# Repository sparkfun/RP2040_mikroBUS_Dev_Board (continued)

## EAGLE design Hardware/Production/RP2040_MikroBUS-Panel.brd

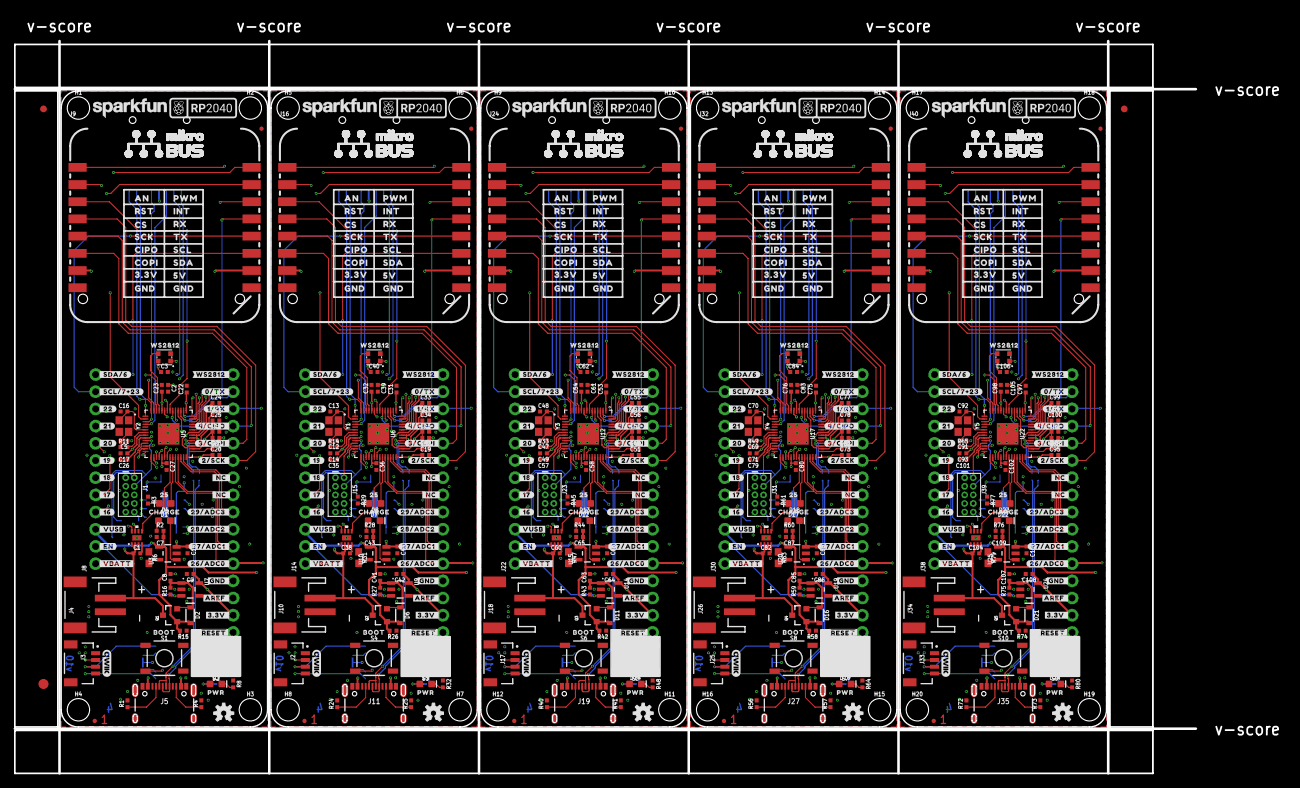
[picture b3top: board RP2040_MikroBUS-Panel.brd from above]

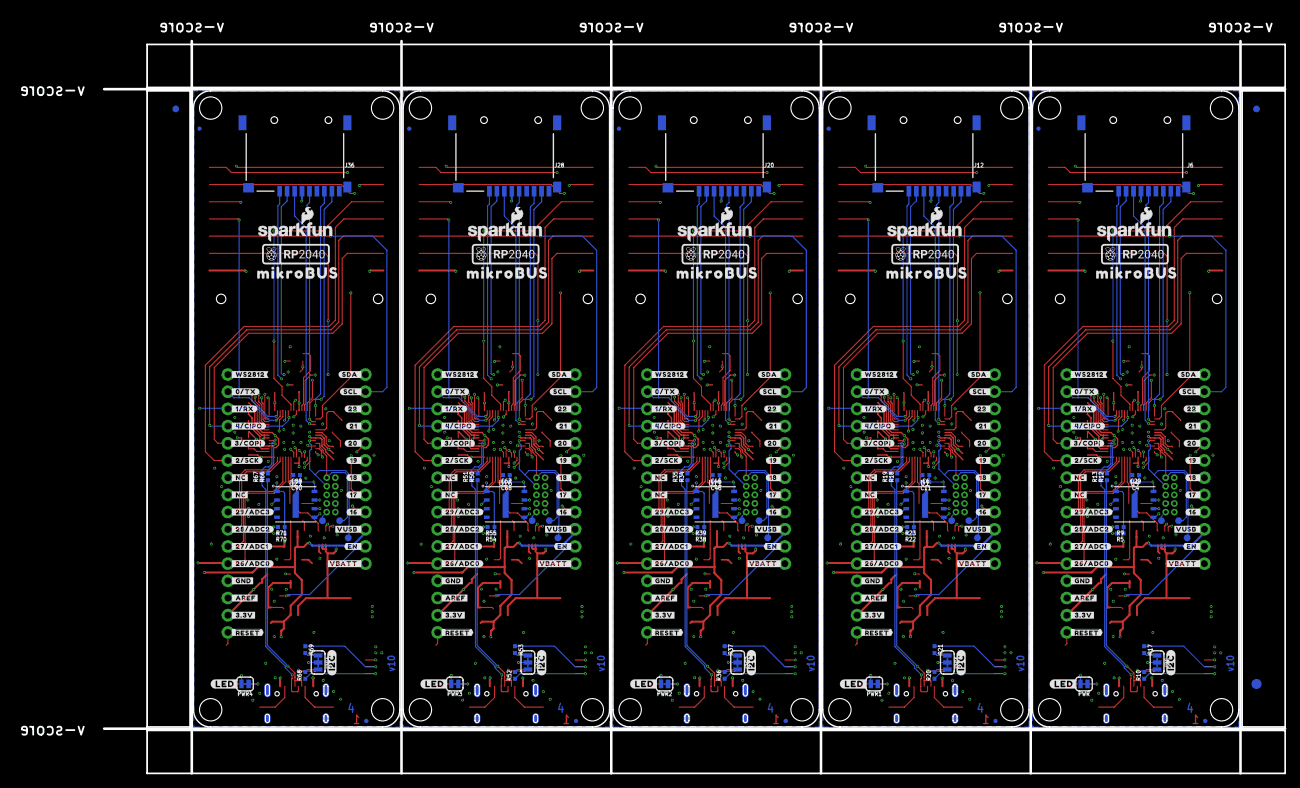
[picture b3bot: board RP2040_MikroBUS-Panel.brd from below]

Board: 4 copper layers, 174.5 x 108.2 mm, 801 parts (253 on the bottom side), 325 nets.

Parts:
C1, C2, C3, C6, C14, C15, C17, C18, C19, C20, C21, C22, C23, C24, C25, C29, C30, C31, C32, C33, C34, C38, C39, C40, C45, C49, C50, C51, C52, C53, C54, C55, C56, C60, C61, C62, C67, C71, C72, C73, C74, C75, C76, C77, C78, C82, C83, C84, C89, C93, C94, C95, C96, C97, C98, C99, C100, C104, C105, C106: 0.1uF; 0402-TIGHT
C4, C9, C11, C26, C27, C28, C35, C36, C37, C42, C46, C57, C58, C59, C64, C68, C79, C80, C81, C86, C90, C101, C102, C103, C108: 2.2uF; 0402-TIGHT
C5, C12, C13, C16, C47, C48, C69, C70, C91, C92: 15pF; 0402-TIGHT
C7, C10, C43, C44, C65, C66, C87, C88, C109, C110: 4.7uF; 0402-TIGHT
C8, C41, C63, C85, C107: 1.0uF; 0402-TIGHT
D1, D7, D12, D17, D22: Yellow; LED-0603
D2, D6, D11, D16, D21: 1A/23V/620mV; SOD-323
D3, D9, D14, D19, D24: RED; LED-0603
D4, D8, D13, D18, D23: BLUE; LED-0603
D5, D10, D15, D20, D25: WS2812_2020; WS2812-2020
E$1, E$2, E$3, E$4: FIDUCIAL-1X2
E$5, E$6: FIDUCIAL-1.5X3
FD1, FD2, FD3, FD4, FD5, FD6, FD7, FD8, FD9, FD10, FD11, FD12, FD13, FD14, FD15, FD16, FD17, FD18, FD19, FD20: FIDUCIALUFIDUCIAL; FIDUCIAL-MICRO
H1, H2, H3, H4, H5, H6, H7, H8, H9, H10, H11, H12, H13, H14, H15, H16, H17, H18, H19, H20: STAND-OFF
I2C, I2C1, I2C2, I2C3, I2C4: JUMPER-SMT_3_2-NC_TRACE_SILK; SMT-JUMPER_3_2-NC_TRACE_SILK
J1, J15, J23, J31, J39: SWD; 2X5-PTH-1.27MM
J2, J3, J17, J25, J33: Qwiic; JST04_1MM_RA
J4, J10, J18, J26, J34: JST-2-SMD
J5, J11, J19, J27, J35: USB C; USB-C-16P-4LAYER-ISOLATED
J6, J12, J20, J28, J36: microSD; MICROSD-EXTERNALPIN
J7, J13, J21, J29, J37: 1X16_NO_SILK
J8, J14, J22, J30, J38: 1X12_NO_SILK
J9, J16, J24, J32, J40: MIKROBUS_SMD_BLACK1; MIKROBUS_SMD_BLACK
LOGO1, LOGO3, LOGO5, LOGO7, LOGO9: OSHW-LOGOS; OSHW-LOGO-S
LOGO2, LOGO4, LOGO6, LOGO8, LOGO10: SFE_LOGO_NAME.1_INCH; SFE_LOGO_NAME_.1
PWR, PWR1, PWR2, PWR3, PWR4: JUMPER-SMT_2_NC_TRACE_SILK; SMT-JUMPER_2_NC_TRACE_SILK
Q1, Q2, Q3, Q4, Q5: 20V/4.2A/52mΩ/1.4W; SOT23-3
R1, R4, R24, R25, R40, R41, R56, R57, R72, R73: 5.1k; 0402-TIGHT
R2, R3, R5, R8, R11, R14, R22, R28, R29, R32, R33, R38, R44, R45, R48, R49, R54, R60, R61, R64, R65, R70, R76, R77, R80: 1k; 0402-TIGHT
R6, R31, R47, R63, R79: 2.0k; 0603
R7, R30, R46, R62, R78: 200OHM-0402T-1/16W-1%; 0402-TIGHT
R9, R15, R16, R23, R26, R27, R39, R42, R43, R55, R58, R59, R71, R74, R75: 10k; 0402-TIGHT
R10, R17, R20, R21, R36, R37, R52, R53, R68, R69: 2.2k; 0402-TIGHT
R12, R13, R18, R19, R34, R35, R50, R51, R66, R67: 27; 0402-TIGHT
S1, S2, S3, S4, S5, S6, S7, S8, S9, S10: MOMENTARY-SWITCH-SPST-SMD-5.2MM-TALL; TACTILE_SWITCH_SMD_5.2MM
TP1, TP2, TP3, TP4, TP5, TP6, TP7, TP8, TP9, TP10, TP11, TP12, TP13, TP14, TP15: TEST-POINT3X4; PAD.03X.04
U1, U4, U11, U16, U21: W25QXX128MBIT; WSON-8-6X5-SKINNY_CENTERPAD
U2, U8, U13, U18, U23: MAX17048; DFN-8
U3, U10, U15, U20, U25: MCP73831; SOT23-5
U5, U6, U12, U17, U22: RP2040; QFN-56
U7, U9, U14, U19, U24: 3.3V; SOT23-5
U$1, U$31, U$169, U$253, U$337: #_16#0
U$2, U$46, U$170, U$254, U$338: #_17#0
U$3, U$86, U$171, U$255, U$339: #_18#0
U$4, U$87, U$172, U$256, U$340: #_19#0
U$5, U$89, U$173, U$257, U$341: #_20#0
U$6, U$90, U$174, U$258, U$342: #_21#0
U$7, U$91, U$175, U$259, U$343: #_22#0
U$8, U$98, U$182, U$266, U$350: #_SCL#7#23#0
U$9, U$99, U$183, U$267, U$351: #_SDA#6#0
U$10, U$92, U$176, U$260, U$344: #WS2812_#0
U$11, U$93, U$177, U$261, U$345: #0#TX_#0
U$12, U$94, U$178, U$262, U$346: #1#RX_#0
U$13, U$95, U$179, U$263, U$347: #4#CIPO_#0
U$14, U$96, U$180, U$264, U$348: #3#COPI_#0
U$15, U$97, U$181, U$265, U$349: #2#SCK_#0
U$16, U$138, U$222, U$306, U$390: PWR0
U$17, U$73, U$148, U$149, U$232, U$233, U$316, U$317, U$400, U$401: RASPI_RP2040_LOGO_10MM
U$18, U$100, U$184, U$268, U$352: #29#ADC3_#0
U$19, U$101, U$185, U$269, U$353: #28#ADC2_#0
U$20, U$102, U$186, U$270, U$354: #27#ADC1_#0
U$21, U$103, U$187, U$271, U$355: #26#ADC0_#0
U$22, U$104, U$188, U$272, U$356: #_VUSB#0
U$23, U$105, U$189, U$273, U$357: #_EN#0
U$24, U$106, U$190, U$274, U$358: #_VBATT#0
U$25, U$107, U$191, U$275, U$359: #GND_#0
U$26, U$108, U$192, U$276, U$360: #AREF_#0
U$27, U$109, U$193, U$277, U$361: #3#3V_#0
U$28, U$110, U$194, U$278, U$362: ##RESET##0
U$29, U$151, U$235, U$319, U$403: AN0
U$30, U$150, U$234, U$318, U$402: WS28120
U$32, U$112, U$196, U$280, U$364: SFE_LOGO_NAME_FLAME_.1
U$33, U$126, U$210, U$294, U$378: #SCL_#0
U$34, U$127, U$211, U$295, U$379: #SDA_#0
U$35, U$128, U$212, U$296, U$380: #_#RESET##0
U$36, U$129, U$213, U$297, U$381: #_3#3V#0
U$37, U$130, U$214, U$298, U$382: #_AREF#0
U$38, U$131, U$215, U$299, U$383: #_GND#0
U$39, U$132, U$216, U$300, U$384: #_26#ADC0#0
U$40, U$133, U$217, U$301, U$385: #_27#ADC1#0
U$41, U$134, U$218, U$302, U$386: #_28#ADC2#0
U$42, U$135, U$219, U$303, U$387: #_29#ADC3#0
U$43, U$168, U$252, U$336, U$420: #LED#0
U$44, U$152, U$236, U$320, U$404: RST0
U$45, U$153, U$237, U$321, U$405: CS0
U$47, U$48, U$139, U$140, U$223, U$224, U$307, U$308, U$391, U$392: #_NC_#0
U$49, U$141, U$225, U$309, U$393: #_2#SCK#0
U$50, U$142, U$226, U$310, U$394: #_3#COPI#0
U$51, U$143, U$227, U$311, U$395: #_4#CIPO#0
U$52, U$144, U$228, U$312, U$396: #_1#RX#0
U$53, U$145, U$229, U$313, U$397: #_0#TX#0
U$54, U$113, U$197, U$281, U$365: 250
U$55, U$114, U$198, U$282, U$366: CHARGE0
U$56, U$115, U$199, U$283, U$367: BOOT0
U$57, U$116, U$200, U$284, U$368: #22_#0
U$58, U$117, U$201, U$285, U$369: #21_#0
U$59, U$118, U$202, U$286, U$370: #20_#0
U$60, U$154, U$238, U$322, U$406: CIPO0
U$61, U$119, U$203, U$287, U$371: #19_#0
U$62, U$120, U$204, U$288, U$372: #18_#0
U$63, U$121, U$205, U$289, U$373: #17_#0
U$64, U$111, U$195, U$279, U$363: QWIIC_4MM
U$65, U$122, U$206, U$290, U$374: #16_#0
U$66, U$123, U$207, U$291, U$375: #VUSB_#0
U$67, U$124, U$208, U$292, U$376: #EN_#0
U$68, U$125, U$209, U$293, U$377: #VBATT_#0
U$69, U$70, U$136, U$137, U$220, U$221, U$304, U$305, U$388, U$389: #_NC#0
U$71, U$146, U$230, U$314, U$398: #_WS2812#0
U$72, U$147, U$231, U$315, U$399: #I2C#0
U$74, U$155, U$239, U$323, U$407: SCK0
U$75, U$156, U$240, U$324, U$408: COPI0
U$76, U$157, U$241, U$325, U$409: 3#3V0
U$77, U$78, U$158, U$159, U$242, U$243, U$326, U$327, U$410, U$411: GND0
U$79, U$160, U$244, U$328, U$412: 5V0
U$80, U$161, U$245, U$329, U$413: SDA0
U$81, U$162, U$246, U$330, U$414: SCL0
U$82, U$163, U$247, U$331, U$415: TX0
U$83, U$164, U$248, U$332, U$416: RX0
U$84, U$165, U$249, U$333, U$417: INT0
U$85, U$166, U$250, U$334, U$418: PWM0
U$88, U$167, U$251, U$335, U$419: MIKROBUS0
Y1, Y2, Y3, Y4, Y5: 12MHz; CRYSTAL-SMD-2X2.5MM

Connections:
1.1V: C24.1, C25.1, C26.1, U5.23, U5.45, U5.50
1.1V1: C33.1, C34.1, C35.1, U6.23, U6.45, U6.50
1.1V2: C55.1, C56.1, C57.1, U12.23, U12.45, U12.50
1.1V3: C77.1, C78.1, C79.1, U17.23, U17.45, U17.50
1.1V4: C99.1, C100.1, C101.1, U22.23, U22.45, U22.50
3.3V: C2.1, C3.1, C4.1, C9.1, C17.1, C18.1, C20.1, C21.1, C22.1, C23.1, C27.1, C29.1, D5.VCC, I2C.2, J1.1, J3.2, J6.4, J7.2, J9.7, PWR.2, R7.2, R9.2, U4.8, U5.1, U5.10, U5.22, U5.33, U5.42, U5.44, U5.48, U5.49, U7.5
3.3V1: C6.1, C11.1, C14.1, C15.1, C19.1, C30.1, C31.1, C32.1, C36.1, C39.1, C40.1, C42.1, D10.VCC, I2C1.2, J2.2, J12.4, J13.2, J15.1, J16.7, PWR1.2, R23.2, R30.2, U1.8, U6.1, U6.10, U6.22, U6.33, U6.42, U6.44, U6.48, U6.49, U9.5
3.3V2: C45.1, C46.1, C49.1, C50.1, C51.1, C52.1, C53.1, C54.1, C58.1, C61.1, C62.1, C64.1, D15.VCC, I2C2.2, J17.2, J20.4, J21.2, J23.1, J24.7, PWR2.2, R39.2, R46.2, U11.8, U12.1, U12.10, U12.22, U12.33, U12.42, U12.44, U12.48, U12.49, U14.5
3.3V3: C67.1, C68.1, C71.1, C72.1, C73.1, C74.1, C75.1, C76.1, C80.1, C83.1, C84.1, C86.1, D20.VCC, I2C3.2, J25.2, J28.4, J29.2, J31.1, J32.7, PWR3.2, R55.2, R62.2, U16.8, U17.1, U17.10, U17.22, U17.33, U17.42, U17.44, U17.48, U17.49, U19.5
3.3V4: C89.1, C90.1, C93.1, C94.1, C95.1, C96.1, C97.1, C98.1, C102.1, C105.1, C106.1, C108.1, D25.VCC, I2C4.2, J33.2, J36.4, J37.2, J39.1, J40.7, PWR4.2, R71.2, R78.2, U21.8, U22.1, U22.10, U22.22, U22.33, U22.42, U22.44, U22.48, U22.49, U24.5
!BATT_ALERT!: U2.5, U5.36
!BATT_ALERT!1: U6.36, U8.5
!BATT_ALERT!2: U12.36, U13.5
!BATT_ALERT!3: U17.36, U18.5
!BATT_ALERT!4: U22.36, U23.5
!BOOT!: R5.2, S1.3
!BOOT!1: R22.2, S4.3
!BOOT!2: R38.2, S6.3
!BOOT!3: R54.2, S8.3
!BOOT!4: R70.2, S10.3
!QSPI-CS!: R5.1, R9.1, U4.1, U5.56
!QSPI-CS!1: R22.1, R23.1, U1.1, U6.56
!QSPI-CS!2: R38.1, R39.1, U11.1, U12.56
!QSPI-CS!3: R54.1, R55.1, U16.1, U17.56
!QSPI-CS!4: R70.1, R71.1, U21.1, U22.56
!RESET!: J1.10, J7.1, S2.3, TP3.1, U5.26
!RESET!1: J13.1, J15.10, S3.3, TP6.1, U6.26
!RESET!2: J21.1, J23.10, S5.3, TP9.1, U12.26
!RESET!3: J29.1, J31.10, S7.3, TP12.1, U17.26
!RESET!4: J37.1, J39.10, S9.3, TP15.1, U22.26
!SPI0_CS!: J9.3, U5.7
!SPI0_CS!1: J16.3, U6.7
!SPI0_CS!2: J24.3, U12.7
!SPI0_CS!3: J32.3, U17.7
!SPI0_CS!4: J40.3, U22.7
ADC0: J7.5, J9.1, U5.38
ADC1: J7.6, U5.39
ADC2: J7.7, U5.40
ADC3: J7.8, U5.41
ADC4: J13.8, U6.41
ADC5: J13.5, J16.1, U6.38
ADC6: J13.6, U6.39
ADC7: J13.7, U6.40
ADC8: J21.8, U12.41
ADC9: J21.5, J24.1, U12.38
ADC10: J21.6, U12.39
ADC11: J21.7, U12.40
ADC12: J29.8, U17.41
ADC13: J29.5, J32.1, U17.38
ADC14: J29.6, U17.39
ADC15: J29.7, U17.40
ADC16: J37.8, U22.41
ADC17: J37.5, J40.1, U22.38
ADC18: J37.6, U22.39
ADC19: J37.7, U22.40
AVDD: C28.1, J7.3, R7.1, U5.43
AVDD1: C37.1, J13.3, R30.1, U6.43
AVDD2: C59.1, J21.3, R46.1, U12.43
AVDD3: C81.1, J29.3, R62.1, U17.43
AVDD4: C103.1, J37.3, R78.1, U22.43
EN: J8.2, R16.1, U7.3
EN1: J14.2, R27.1, U9.3
EN2: J22.2, R43.1, U14.3
EN3: J30.2, R59.1, U19.3
EN4: J38.2, R75.1, U24.3
GND: C1.2, C2.2, C3.2, C4.2, C5.1, C7.2, C8.2, C9.2, C10.2, C16.1, C17.2, C18.2, C20.2, C21.2, C22.2, C23.2, C24.2, C25.2, C26.2, C27.2, C28.2, C29.2, D5.GND, J1.3, J1.5, J1.9, J3.1, J4.1, J5.GND, J5.GND2, J6.6, J6.9, J6.10, J6.11, J6.12, J6.13, J7.4, J9.8, J9.9, R1.2, R3.1, R4.2, R6.1, R8.1, R15.1, S1.1, S2.1, U2.1, U2.4, U2.6, U2.9, U3.2, U4.4, U5.19, U5.EPAD, U7.2
GND1: C6.2, C11.2, C12.1, C13.1, C14.2, C15.2, C19.2, C30.2, C31.2, C32.2, C33.2, C34.2, C35.2, C36.2, C37.2, C38.2, C39.2, C40.2, C41.2, C42.2, C43.2, C44.2, D10.GND, J2.1, J10.1, J11.GND, J11.GND2, J12.6, J12.9, J12.10, J12.11, J12.12, J12.13, J13.4, J15.3, J15.5, J15.9, J16.8, J16.9, R24.2, R25.2, R26.1, R29.1, R31.1, R32.1, S3.1, S4.1, U1.4, U6.19, U6.EPAD, U8.1, U8.4, U8.6, U8.9, U9.2, U10.2
GND2: C45.2, C46.2, C47.1, C48.1, C49.2, C50.2, C51.2, C52.2, C53.2, C54.2, C55.2, C56.2, C57.2, C58.2, C59.2, C60.2, C61.2, C62.2, C63.2, C64.2, C65.2, C66.2, D15.GND, J17.1, J18.1, J19.GND, J19.GND2, J20.6, J20.9, J20.10, J20.11, J20.12, J20.13, J21.4, J23.3, J23.5, J23.9, J24.8, J24.9, R40.2, R41.2, R42.1, R45.1, R47.1, R48.1, S5.1, S6.1, U11.4, U12.19, U12.EPAD, U13.1, U13.4, U13.6, U13.9, U14.2, U15.2
GND3: C67.2, C68.2, C69.1, C70.1, C71.2, C72.2, C73.2, C74.2, C75.2, C76.2, C77.2, C78.2, C79.2, C80.2, C81.2, C82.2, C83.2, C84.2, C85.2, C86.2, C87.2, C88.2, D20.GND, J25.1, J26.1, J27.GND, J27.GND2, J28.6, J28.9, J28.10, J28.11, J28.12, J28.13, J29.4, J31.3, J31.5, J31.9, J32.8, J32.9, R56.2, R57.2, R58.1, R61.1, R63.1, R64.1, S7.1, S8.1, U16.4, U17.19, U17.EPAD, U18.1, U18.4, U18.6, U18.9, U19.2, U20.2
GND4: C89.2, C90.2, C91.1, C92.1, C93.2, C94.2, C95.2, C96.2, C97.2, C98.2, C99.2, C100.2, C101.2, C102.2, C103.2, C104.2, C105.2, C106.2, C107.2, C108.2, C109.2, C110.2, D25.GND, J33.1, J34.1, J35.GND, J35.GND2, J36.6, J36.9, J36.10, J36.11, J36.12, J36.13, J37.4, J39.3, J39.5, J39.9, J40.8, J40.9, R72.2, R73.2, R74.1, R77.1, R79.1, R80.1, S9.1, S10.1, U21.4, U22.19, U22.EPAD, U23.1, U23.4, U23.6, U23.9, U24.2, U25.2
GPIO1: J14.4, J16.16, U6.27
GPIO2: J14.5, J16.15, U6.28
GPIO3: J14.6, U6.29
GPIO4: J14.7, U6.30
GPIO5: J14.8, U6.31
GPIO6: J14.9, U6.32
GPIO7: J14.10, U6.34
GPIO8: J16.2, U6.16
GPIO9: J22.4, J24.16, U12.27
GPIO10: J22.5, J24.15, U12.28
GPIO11: J22.6, U12.29
GPIO12: J22.7, U12.30
GPIO13: J9.2, U5.16
GPIO14: J22.8, U12.31
GPIO15: J22.9, U12.32
GPIO16: J8.4, J9.16, U5.27
GPIO17: J8.5, J9.15, U5.28
GPIO18: J8.6, U5.29
GPIO19: J8.7, U5.30
GPIO20: J8.8, U5.31
GPIO21: J8.9, U5.32
GPIO22: J8.10, U5.34
GPIO23: J22.10, U12.34
GPIO24: J24.2, U12.16
GPIO25: J30.4, J32.16, U17.27
GPIO26: J30.5, J32.15, U17.28
GPIO27: J30.6, U17.29
GPIO28: J30.7, U17.30
GPIO29: J30.8, U17.31
GPIO30: J30.9, U17.32
GPIO31: J30.10, U17.34
GPIO32: J32.2, U17.16
GPIO33: J38.4, J40.16, U22.27
GPIO34: J38.5, J40.15, U22.28
GPIO35: J38.6, U22.29
GPIO36: J38.7, U22.30
GPIO37: J38.8, U22.31
GPIO38: J38.9, U22.32
GPIO39: J38.10, U22.34
GPIO40: J40.2, U22.16
I2C1_SCL/GPIO1: J2.4, J14.11, J16.12, R20.1, U6.9, U6.35, U8.7
I2C1_SCL/GPIO2: J17.4, J22.11, J24.12, R36.1, U12.9, U12.35, U13.7
I2C1_SCL/GPIO3: J25.4, J30.11, J32.12, R52.1, U17.9, U17.35, U18.7
I2C1_SCL/GPIO4: J33.4, J38.11, J40.12, R68.1, U22.9, U22.35, U23.7
I2C1_SCL/GPIO23: J3.4, J8.11, J9.12, R10.1, U2.7, U5.9, U5.35
I2C1_SDA: J3.3, J8.12, J9.11, R17.1, U2.8, U5.8
I2C1_SDA1: J2.3, J14.12, J16.11, R21.1, U6.8, U8.8
I2C1_SDA2: J17.3, J22.12, J24.11, R37.1, U12.8, U13.8
I2C1_SDA3: J25.3, J30.12, J32.11, R53.1, U17.8, U18.8
I2C1_SDA4: J33.3, J38.12, J40.11, R69.1, U22.8, U23.8
LED_BUILTIN: D4.A, U5.37
LED_BUILTIN1: D8.A, U6.37
LED_BUILTIN2: D13.A, U12.37
LED_BUILTIN3: D18.A, U17.37
LED_BUILTIN4: D23.A, U22.37
unnamed: D4.C, R3.2
unnamed: I2C.3, R10.2
unnamed: I2C.1, R17.2
unnamed: R11.2, U5.21
unnamed: C16.2, U5.20, Y2.P3
unnamed: C5.2, R11.1, Y2.P1
unnamed: D3.C, R8.2
unnamed: D7.C, U10.1
unnamed: D1.C, U3.1
unnamed: D3.A, PWR.1
unnamed: J5.A5, R1.1
unnamed: J5.B5, R4.1
unnamed: R31.2, U10.5
unnamed: R6.2, U3.5
unnamed: C8.1, D2.C, Q1.2, R16.2, U7.1
unnamed: D7.A, R28.1
unnamed: D1.A, R2.1
unnamed: D8.C, R29.2
unnamed: I2C1.3, R20.2
unnamed: I2C1.1, R21.2
unnamed: R14.2, U6.21
unnamed: C13.2, U6.20, Y1.P3
unnamed: C12.2, R14.1, Y1.P1
unnamed: J11.A5, R24.1
unnamed: J11.B5, R25.1
unnamed: C41.1, D6.C, Q2.2, R27.2, U9.1
unnamed: D9.C, R32.2
unnamed: D9.A, PWR1.1
unnamed: D12.C, U15.1
unnamed: R47.2, U15.5
unnamed: D12.A, R44.1
unnamed: D13.C, R45.2
unnamed: I2C2.3, R36.2
unnamed: I2C2.1, R37.2
unnamed: R33.2, U12.21
unnamed: C48.2, U12.20, Y3.P3
unnamed: C47.2, R33.1, Y3.P1
unnamed: J19.A5, R40.1
unnamed: J19.B5, R41.1
unnamed: C63.1, D11.C, Q3.2, R43.2, U14.1
unnamed: D14.C, R48.2
unnamed: D14.A, PWR2.1
unnamed: D17.C, U20.1
unnamed: R63.2, U20.5
unnamed: D17.A, R60.1
unnamed: D18.C, R61.2
unnamed: I2C3.3, R52.2
unnamed: I2C3.1, R53.2
unnamed: R49.2, U17.21
unnamed: C70.2, U17.20, Y4.P3
unnamed: C69.2, R49.1, Y4.P1
unnamed: J27.A5, R56.1
unnamed: J27.B5, R57.1
unnamed: C85.1, D16.C, Q4.2, R59.2, U19.1
unnamed: D19.C, R64.2
unnamed: D19.A, PWR3.1
unnamed: D22.C, U25.1
unnamed: R79.2, U25.5
unnamed: D22.A, R76.1
unnamed: D23.C, R77.2
unnamed: I2C4.3, R68.2
unnamed: I2C4.1, R69.2
unnamed: R65.2, U22.21
unnamed: C92.2, U22.20, Y5.P3
unnamed: C91.2, R65.1, Y5.P1
unnamed: J35.A5, R72.1
unnamed: J35.B5, R73.1
unnamed: C107.1, D21.C, Q5.2, R75.2, U24.1
unnamed: D24.C, R80.2
unnamed: D24.A, PWR4.1
QSPI-0: U4.5, U5.53
QSPI-1: U4.2, U5.55
QSPI-2: U4.3, U5.54
QSPI-3: U4.7, U5.51
QSPI-4: U1.5, U6.53
QSPI-5: U1.7, U6.51
QSPI-6: U1.2, U6.55
QSPI-7: U1.3, U6.54
QSPI-8: U11.5, U12.53
QSPI-9: U11.7, U12.51
QSPI-10: U11.2, U12.55
QSPI-11: U11.3, U12.54
QSPI-12: U16.5, U17.53
QSPI-13: U16.7, U17.51
QSPI-14: U16.2, U17.55
QSPI-15: U16.3, U17.54
QSPI-16: U21.5, U22.53
QSPI-17: U21.7, U22.51
QSPI-18: U21.2, U22.55
QSPI-19: U21.3, U22.54
QSPI-CLK: U4.6, U5.52
QSPI-CLK1: U1.6, U6.52
QSPI-CLK2: U11.6, U12.52
QSPI-CLK3: U16.6, U17.52
QSPI-CLK4: U21.6, U22.52
SDIO_DAT1: J6.8, U5.14
SDIO_DAT2: J6.1, U5.13
SDIO_DAT3: J12.8, U6.14
SDIO_DAT4: J12.1, U6.13
SDIO_DAT5: J20.8, U12.14
SDIO_DAT6: J20.1, U12.13
SDIO_DAT7: J28.8, U17.14
SDIO_DAT8: J28.1, U17.13
SDIO_DAT9: J36.8, U22.14
SDIO_DAT10: J36.1, U22.13
SPI0_CIPO: J7.13, J9.5, U5.6
SPI0_CIPO1: J13.13, J16.5, U6.6
SPI0_CIPO2: J21.13, J24.5, U12.6
SPI0_CIPO3: J29.13, J32.5, U17.6
SPI0_CIPO4: J37.13, J40.5, U22.6
SPI0_COPI: J7.12, J9.6, U5.5
SPI0_COPI1: J13.12, J16.6, U6.5
SPI0_COPI2: J21.12, J24.6, U12.5
SPI0_COPI3: J29.12, J32.6, U17.5
SPI0_COPI4: J37.12, J40.6, U22.5
SPI0_SCK: J7.11, J9.4, U5.4
SPI0_SCK1: J13.11, J16.4, U6.4
SPI0_SCK2: J21.11, J24.4, U12.4
SPI0_SCK3: J29.11, J32.4, U17.4
SPI0_SCK4: J37.11, J40.4, U22.4
SPI_!CS1!/SDIO_DAT1: J12.2, U6.12
SPI_!CS1!/SDIO_DAT2: J20.2, U12.12
SPI_!CS1!/SDIO_DAT3: J6.2, U5.12
SPI_!CS1!/SDIO_DAT4: J28.2, U17.12
SPI_!CS1!/SDIO_DAT5: J36.2, U22.12
SPI_CIPO1/SDIO_DAT0: J6.7, U5.15
SPI_CIPO1/SDIO_DAT1: J12.7, U6.15
SPI_CIPO1/SDIO_DAT2: J20.7, U12.15
SPI_CIPO1/SDIO_DAT3: J28.7, U17.15
SPI_CIPO1/SDIO_DAT4: J36.7, U22.15
SPI_COPI1/SDIO_CMD: J6.3, U5.18
SPI_COPI1/SDIO_CMD1: J12.3, U6.18
SPI_COPI1/SDIO_CMD2: J20.3, U12.18
SPI_COPI1/SDIO_CMD3: J28.3, U17.18
SPI_COPI1/SDIO_CMD4: J36.3, U22.18
SPI_SCK1/SDIO_CLK: J6.5, U5.17
SPI_SCK1/SDIO_CLK1: J12.5, U6.17
SPI_SCK1/SDIO_CLK2: J20.5, U12.17
SPI_SCK1/SDIO_CLK3: J28.5, U17.17
SPI_SCK1/SDIO_CLK4: J36.5, U22.17
SWDCK: J1.4, TP1.1, U5.24
SWDCK1: J15.4, TP4.1, U6.24
SWDCK2: J23.4, TP7.1, U12.24
SWDCK3: J31.4, TP10.1, U17.24
SWDCK4: J39.4, TP13.1, U22.24
SWDIO: J1.2, TP2.1, U5.25
SWDIO1: J15.2, TP5.1, U6.25
SWDIO2: J23.2, TP8.1, U12.25
SWDIO3: J31.2, TP11.1, U17.25
SWDIO4: J39.2, TP14.1, U22.25
UART0_RX: J7.14, J9.14, U5.3
UART0_RX1: J13.14, J16.14, U6.3
UART0_RX2: J21.14, J24.14, U12.3
UART0_RX3: J29.14, J32.14, U17.3
UART0_RX4: J37.14, J40.14, U22.3
UART0_TX: J7.15, J9.13, U5.2
UART0_TX1: J13.15, J16.13, U6.2
UART0_TX2: J21.15, J24.13, U12.2
UART0_TX3: J29.15, J32.13, U17.2
UART0_TX4: J37.15, J40.13, U22.2
USB_F_N: R12.2, U5.46
USB_F_N1: R18.2, U6.46
USB_F_N2: R34.2, U12.46
USB_F_N3: R50.2, U17.46
USB_F_N4: R66.2, U22.46
USB_F_P: R13.2, U5.47
USB_F_P1: R19.2, U6.47
USB_F_P2: R35.2, U12.47
USB_F_P3: R51.2, U17.47
USB_F_P4: R67.2, U22.47
USB_N: J5.A7, J5.B7, R12.1
USB_N1: J11.A7, J11.B7, R18.1
USB_N2: J19.A7, J19.B7, R34.1
USB_N3: J27.A7, J27.B7, R50.1
USB_N4: J35.A7, J35.B7, R66.1
USB_P: J5.A6, J5.B6, R13.1
USB_P1: J11.A6, J11.B6, R19.1
USB_P2: J19.A6, J19.B6, R35.1
USB_P3: J27.A6, J27.B6, R51.1
USB_P4: J35.A6, J35.B6, R67.1
V_BATT: C1.1, C10.1, J4.2, J8.1, Q1.3, U2.2, U2.3, U3.3
V_BATT1: C38.1, C44.1, J10.2, J14.1, Q2.3, U8.2, U8.3, U10.3
V_BATT2: C60.1, C66.1, J18.2, J22.1, Q3.3, U13.2, U13.3, U15.3
V_BATT3: C82.1, C88.1, J26.2, J30.1, Q4.3, U18.2, U18.3, U20.3
V_BATT4: C104.1, C110.1, J34.2, J38.1, Q5.3, U23.2, U23.3, U25.3
V_USB: C7.1, D2.A, J5.VBUS1, J5.VBUS2, J8.3, J9.10, Q1.1, R2.2, R15.2, U3.4
V_USB1: C43.1, D6.A, J11.VBUS1, J11.VBUS2, J14.3, J16.10, Q2.1, R26.2, R28.2, U10.4
V_USB2: C65.1, D11.A, J19.VBUS1, J19.VBUS2, J22.3, J24.10, Q3.1, R42.2, R44.2, U15.4
V_USB3: C87.1, D16.A, J27.VBUS1, J27.VBUS2, J30.3, J32.10, Q4.1, R58.2, R60.2, U20.4
V_USB4: C109.1, D21.A, J35.VBUS1, J35.VBUS2, J38.3, J40.10, Q5.1, R74.2, R76.2, U25.4
WS2812_DI: D5.DI, U5.11
WS2812_DI1: D10.DI, U6.11
WS2812_DI2: D15.DI, U12.11
WS2812_DI3: D20.DI, U17.11
WS2812_DI4: D25.DI, U22.11
WS2812_DO: D5.DO, J7.16
WS2812_DO1: D10.DO, J13.16
WS2812_DO2: D15.DO, J21.16
WS2812_DO3: D20.DO, J29.16
WS2812_DO4: D25.DO, J37.16

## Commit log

2021-09-14 Initial commit
    Starting with the MicroMod Qwiic Carrier - Single files.
2021-09-23 Added mikroBUS socket to design
2021-09-27 Rename eagle files
    Make sure everything is connected in the schematic
    Parts are laid out where they should be on board, need to just route/re-route.
2021-09-28 Routing finished!
2021-09-28 Made board dimensions on grid
2021-09-28 Space pins for thing plus shields
2021-09-30 Design review
2021-09-30 Add raspi logos to repo
2021-09-30 More of Pete's updates
    * Fix I2C jumper label
    * Update RP2040 logo and add to SF Eagle libraries
    * Change "Mik" to "Mikro" for mikroBUS reset button
2021-09-30 Schematic updates
    * Remove values from TPs
    * Updated net labels with "!" for active low signals - !BOOT!, !SPI0_CS!, !QSPI-CS!, !BATT_ALERT!
    * Updated name, value, and shape of mikroBUS socket sch symbol
    * Switched out SD card socket for the new one, did NOT connect the detect pin
2021-09-30 Board updates
    * Fix RESET button label
    * Add RP2040 to SF microcontroller library and update in sch/board
    * Gave some more space between the new traces I placed
    * Brought D+ and D- traces closer together
    * Changed "WS2812" label to text only
2021-09-30 Run checklist
2021-10-28 MikroE updates
    * Change button label from "Mik Reset" to "Mikroe Reset"
    * Added mikroBUS pin names
2021-11-05 Design review before ordering changes
    * Add a pullup and NC jumper on the CS line
    * A jumper on the PWR LED
2021-11-05 Update silk screen labels and generate gerbers
2021-11-23 Add hardware test sketches
2021-12-02 From MikroE convo
    * Remove mikroe button
    * Remove CS pullup
2021-12-11 Update labels
2021-12-13 From mikroE convo
    * Remove reset button
    * Remove CS pullup
2021-12-13 Design review updates
    * Bump version number
    * Remove CS_PU label from borrom
    * Move SWDCK TP
2021-12-15 QC Double check
    * Added label for PWR jumper
    * Moved GPIO16 via
2021-12-15 Run panelizer and generate gerbers
2021-12-15 Organize files for sparkle
2022-01-12 Added uf2s to the repo
2022-01-25 Update RP2040_MikroBUS.brd
    Add dimensions to measurement layer
2022-01-25 Update RP2040_MikroBUS.brd
    Move text away from measurements area
2022-01-26 Update README.md
    Add product photo
